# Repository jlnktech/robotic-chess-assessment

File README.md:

# robotic-chess-assessment
low cost chess robot

kicad folder contains schematic layout of hall effect detection using DRV5053. Idea is to scan 8 squares (1 row) at once, then repeat for other 7 rows to cut down on time. Each piece must have magnet attached.

pcb123 folder contains schematic layout of IR sensors using QRE1113. Once again, scan 1 row (8 squares) then repeat. Each piece must have reflect material on the bottom and be able to cover the slot on each of the squares.

CAD folder contains the mechanical layout of the xyz table

firmware folder contains arduino test for the z-axis portion

yet to be done is to add the raspberry pi actual chess code

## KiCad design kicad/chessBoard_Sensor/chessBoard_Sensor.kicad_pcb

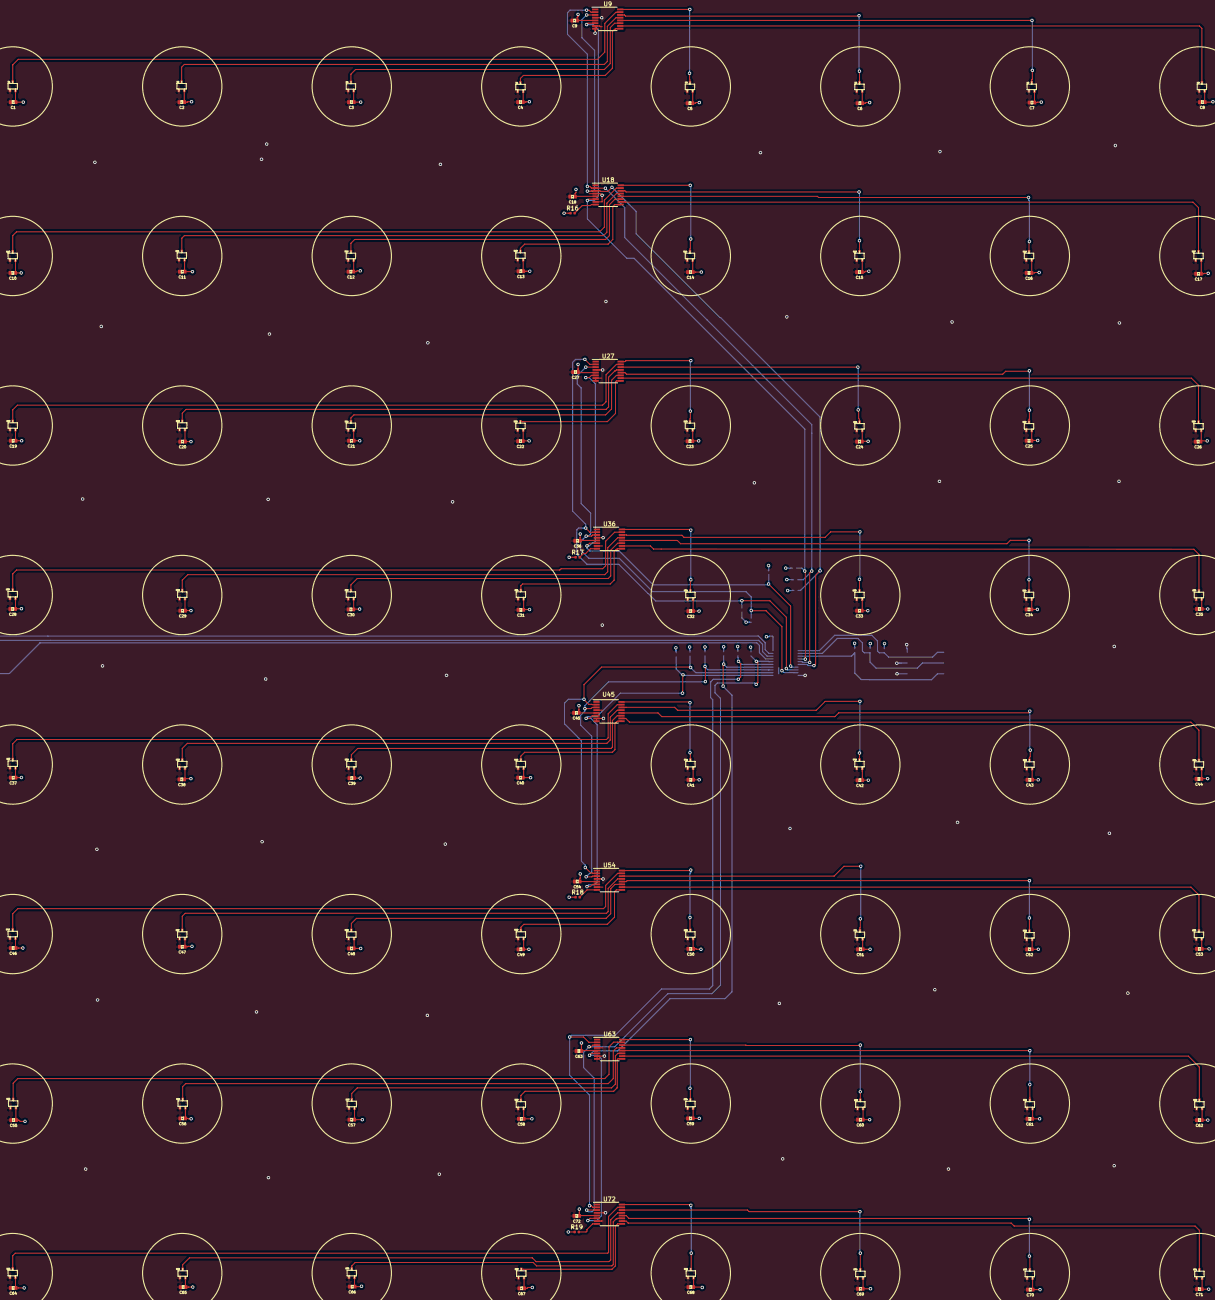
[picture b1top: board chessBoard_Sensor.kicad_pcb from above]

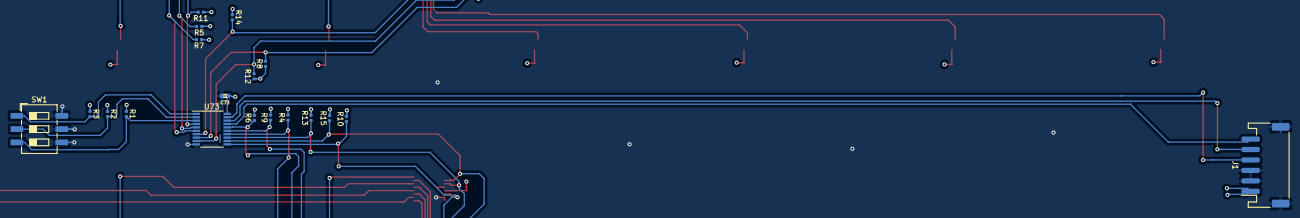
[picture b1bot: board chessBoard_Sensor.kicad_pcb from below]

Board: 4 copper layers, 167 parts (19 on the bottom side), 88 nets.

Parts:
C1, C2, C3, C4, C5, C6, C7, C8, C9, C10, C11, C12, C13, C14, C15, C16, C17, C18, C19, C20, C21, C22, C23, C24, C25, C26, C27, C28, C29, C30, C31, C32, C33, C34, C35, C36, C37, C38, C39, C40, C41, C42, C43, C44, C45, C46, C47, C48, C49, C50, C51, C52, C53, C54, C55, C56, C57, C58, C59, C60, C61, C62, C63, C64, C65, C66, C67, C68, C69, C70, C71, C72, C73: 0.1UF-0402-16V-10%; 0402
J1: HEADER_6; JST_PH_S6B-PH-SM4-TB_1x06-1MP_P2.00mm_Horizontal
R1, R2, R3, R4, R5, R6, R7, R8, R9, R10, R11, R12, R13, R14, R15, R16, R17, R18, R19: 10K, 5%, 402; R_0402_1005Metric
SW1: SW_DIP_x03; SW_DIP_SPSTx03_Slide_6.7x9.18mm_W8.61mm_P2.54mm_LowProfile
U1, U2, U3, U4, U5, U6, U7, U8, U10, U11, U12, U13, U14, U15, U16, U17, U19, U20, U21, U22, U23, U24, U25, U26, U28, U29, U30, U31, U32, U33, U34, U35, U37, U38, U39, U40, U41, U42, U43, U44, U46, U47, U48, U49, U50, U51, U52, U53, U55, U56, U57, U58, U59, U60, U61, U62, U64, U65, U66, U67, U68, U69, U70, U71: DRV5053VAQDBZR; sot323
U9, U18, U27, U36, U45, U54, U63, U72: ADC128D818; TSSOP-16_4.4x5mm_P0.65mm
U73: PCA9544APW; TSSOP-20_4.4x6.5mm_P0.65mm

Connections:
+3V3: C1.1, C2.1, C3.1, C4.1, C5.1, C6.1, C7.1, C8.1, C9.1, C10.1, C11.1, C12.1, C13.1, C14.1, C15.1, C16.1, C17.1, C18.1, C19.1, C20.1, C21.1, C22.1, C23.1, C24.1, C25.1, C26.1, C27.1, C28.1, C29.1, C30.1, C31.1, C32.1, C33.1, C34.1, C35.1, C36.1, C37.1, C38.1, C39.1, C40.1, C41.1, C42.1, C43.1, C44.1, C45.1, C46.1, C47.1, C48.1, C49.1, C50.1, C51.1, C52.1, C53.1, C54.1, C55.1, C56.1, C57.1, C58.1, C59.1, C60.1, C61.1, C62.1, C63.1, C64.1, C65.1, C66.1, C67.1, C68.1, C69.1, C70.1, C71.1, C72.1, C73.1, J1.1, R1.1, R2.1, R3.1, R4.2, R5.1, R6.2, R7.1, R8.1, R9.2, R10.2, R11.1, R12.1, R13.2, R14.1, R15.2, R16.1, R17.1, R18.1, R19.1, U1.3, U2.3, U3.3, U4.3, U5.3, U6.3, U7.3, U8.3, U9.5, U10.3, U11.3, U12.3, U13.3, U14.3, U15.3, U16.3, U17.3, U18.5, U19.3, U20.3, U21.3, U22.3, U23.3, U24.3, U25.3, U26.3, U27.5, U28.3, U29.3, U30.3, U31.3, U32.3, U33.3, U34.3, U35.3, U36.5, U37.3, U38.3, U39.3, U40.3, U41.3, U42.3, U43.3, U44.3, U45.5, U46.3, U47.3, U48.3, U49.3, U50.3, U51.3, U52.3, U53.3, U54.5, U55.3, U56.3, U57.3, U58.3, U59.3, U60.3, U61.3, U62.3, U63.5, U64.3, U65.3, U66.3, U67.3, U68.3, U69.3, U70.3, U71.3, U72.5, U73.20
/Sheet1/INT1: R11.2, U9.6, U18.6, U73.4
/Sheet1/SCL1: R7.2, U9.3, U18.3, U73.6
/Sheet1/SDA1: R5.2, U9.2, U18.2, U73.5
/sheet5C2B8B4A/INT4: R4.1, U63.6, U72.6, U73.14
/sheet5C2B8B4A/SCL4: R6.1, U63.3, U72.3, U73.16
/sheet5C2B8B4A/SDA4: R9.1, U63.2, U72.2, U73.15
/sheet5C2B89C0/INT3: R10.1, U45.6, U54.6, U73.11
/sheet5C2B89C0/SCL3: R13.1, U45.3, U54.3, U73.13
/sheet5C2B89C0/SDA3: R15.1, U45.2, U54.2, U73.12
/sheet5C2B878C/INT2: R14.2, U27.6, U36.6, U73.7
/sheet5C2B878C/SCL2: R12.2, U27.3, U36.3, U73.9
/sheet5C2B878C/SDA2: R8.2, U27.2, U36.2, U73.8
GND: C1.2, C2.2, C3.2, C4.2, C5.2, C6.2, C7.2, C8.2, C9.2, C10.2, C11.2, C12.2, C13.2, C14.2, C15.2, C16.2, C17.2, C18.2, C19.2, C20.2, C21.2, C22.2, C23.2, C24.2, C25.2, C26.2, C27.2, C28.2, C29.2, C30.2, C31.2, C32.2, C33.2, C34.2, C35.2, C36.2, C37.2, C38.2, C39.2, C40.2, C41.2, C42.2, C43.2, C44.2, C45.2, C46.2, C47.2, C48.2, C49.2, C50.2, C51.2, C52.2, C53.2, C54.2, C55.2, C56.2, C57.2, C58.2, C59.2, C60.2, C61.2, C62.2, C63.2, C64.2, C65.2, C66.2, C67.2, C68.2, C69.2, C70.2, C71.2, C72.2, C73.2, J1.2, J1.3, J1.MP, SW1.4, SW1.5, SW1.6, U1.1, U2.1, U3.1, U4.1, U5.1, U6.1, U7.1, U8.1, U9.4, U9.7, U9.8, U10.1, U11.1, U12.1, U13.1, U14.1, U15.1, U16.1, U17.1, U18.4, U18.7, U19.1, U20.1, U21.1, U22.1, U23.1, U24.1, U25.1, U26.1, U27.4, U27.7, U27.8, U28.1, U29.1, U30.1, U31.1, U32.1, U33.1, U34.1, U35.1, U36.4, U36.7, U37.1, U38.1, U39.1, U40.1, U41.1, U42.1, U43.1, U44.1, U45.4, U45.7, U45.8, U46.1, U47.1, U48.1, U49.1, U50.1, U51.1, U52.1, U53.1, U54.4, U54.7, U55.1, U56.1, U57.1, U58.1, U59.1, U60.1, U61.1, U62.1, U63.4, U63.7, U63.8, U64.1, U65.1, U66.1, U67.1, U68.1, U69.1, U70.1, U71.1, U72.4, U72.7, U73.10
unnamed: J1.4, U73.19
unnamed: J1.5, U73.18
unnamed: J1.6, U73.17
unnamed: R1.2, SW1.3, U73.3
unnamed: R2.2, SW1.2, U73.2
unnamed: R3.2, SW1.1, U73.1
unnamed: R16.2, U18.8
unnamed: R17.2, U36.8
unnamed: R18.2, U54.8
unnamed: R19.2, U72.8
unnamed: U1.2, U9.15
unnamed: U2.2, U9.13
unnamed: U3.2, U9.11
unnamed: U4.2, U9.9
unnamed: U5.2, U9.16
unnamed: U6.2, U9.14
unnamed: U7.2, U9.12
unnamed: U8.2, U9.10
unnamed: U10.2, U18.15
unnamed: U11.2, U18.13
unnamed: U12.2, U18.11
unnamed: U13.2, U18.9
unnamed: U14.2, U18.16
unnamed: U15.2, U18.14
unnamed: U16.2, U18.12
unnamed: U17.2, U18.10
unnamed: U19.2, U27.15
unnamed: U20.2, U27.13
unnamed: U21.2, U27.11
unnamed: U22.2, U27.9
unnamed: U23.2, U27.16
unnamed: U24.2, U27.14
unnamed: U25.2, U27.12
unnamed: U26.2, U27.10
unnamed: U28.2, U36.15
unnamed: U29.2, U36.13
unnamed: U30.2, U36.11
unnamed: U31.2, U36.9
unnamed: U32.2, U36.16
unnamed: U33.2, U36.14
unnamed: U34.2, U36.12
unnamed: U35.2, U36.10
unnamed: U37.2, U45.15
unnamed: U38.2, U45.13
unnamed: U39.2, U45.11
unnamed: U40.2, U45.9
unnamed: U41.2, U45.16
unnamed: U42.2, U45.14
unnamed: U43.2, U45.12
unnamed: U44.2, U45.10
unnamed: U46.2, U54.15
unnamed: U47.2, U54.13
unnamed: U48.2, U54.11
unnamed: U49.2, U54.9
unnamed: U50.2, U54.16
unnamed: U51.2, U54.14
unnamed: U52.2, U54.12
unnamed: U53.2, U54.10
unnamed: U55.2, U63.15
unnamed: U56.2, U63.13
unnamed: U57.2, U63.11
unnamed: U58.2, U63.9
unnamed: U59.2, U63.16
unnamed: U60.2, U63.14
unnamed: U61.2, U63.12
unnamed: U62.2, U63.10
unnamed: U64.2, U72.15
unnamed: U65.2, U72.13
unnamed: U66.2, U72.11
unnamed: U67.2, U72.9
unnamed: U68.2, U72.16
unnamed: U69.2, U72.14
unnamed: U70.2, U72.12
unnamed: U71.2, U72.10

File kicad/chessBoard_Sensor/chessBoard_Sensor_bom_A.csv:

Component,Description,Part,References,Value,Footprint,Quantity Per PCB,Datasheet,Field4,Category,Status,Family,MPN,Digi-Key_PN,DK_Datasheet_Link,DK_Detail_Page,Manufacturer
1,0.1uF ceramic capacitors A capacitor is a passive two-terminal electrical component used to store electrical energy temporarily in an electric field.,0.1UF-0402-16V-10%,C1 C2 C3 C4 C5 C6 C7 C8 C9 C10 C11 C12 C13 C14 C15 C16 C17 C18 C19 C20 C21 C22 C23 C24 C25 C26 C27 C28 C29 C30 C31 C32 C33 C34 C35 C36 C37 C38 C39 C40 C41 C42 C43 C44 C45 C46 C47 C48 C49 C50 C51 C52 C53 C54 C55 C56 C57 C58 C59 C60 C61 C62 C63 C64 C65 C66 C67 C68 C69 C70 C71 C72 C73,0.1UF-0402-16V-10%,0402,73,,CAP-12416,,,,,,,,
2,,HEADER_6,J1,HEADER_6,JST_PH_S6B-PH-SM4-TB_1x06-1MP_P2.00mm_Horizontal,1,,,,,,,,,,
3,Resistor,R,R1 R2 R3 R4 R5 R6 R7 R8 R9 R10 R11 R12 R13 R14 R15 R16 R17 R18 R19,"10K, 5%, 402",R_0402_1005Metric,19,~,,,,,,,,,
4,"3x DIP Switch, Single Pole Single Throw (SPST) switch, small symbol",SW_DIP_x03,SW1,SW_DIP_x03,SW_DIP_SPSTx03_Slide_6.7x9.18mm_W8.61mm_P2.54mm_LowProfile,1,,,,,,,,,,
5,"12-Bit, 8-Channel, ADC System Monitor With Temperature Sensor, I2C Interface, TSSOP-16",ADC128D818,U9 U18 U27 U36 U45 U54 U63 U72,ADC128D818,TSSOP-16_4.4x5mm_P0.65mm,8,http://www.ti.com/lit/ds/symlink/adc128d818.pdf,,,,,,,,,
6,SENSOR LINEAR ANALOG SOT23-3,DRV5053VAQDBZR,U1 U2 U3 U4 U5 U6 U7 U8 U10 U11 U12 U13 U14 U15 U16 U17 U19 U20 U21 U22 U23 U24 U25 U26 U28 U29 U30 U31 U32 U33 U34 U35 U37 U38 U39 U40 U41 U42 U43 U44 U46 U47 U48 U49 U50 U51 U52 U53 U55 U56 U57 U58 U59 U60 U61 U62 U64 U65 U66 U67 U68 U69 U70 U71,DRV5053VAQDBZR,sot323,64,http://www.ti.com/lit/ds/symlink/drv5053.pdf,,"Sensors, Transducers",Active,"Magnetic Sensors - Linear, Compass (ICs)",DRV5053VAQDBZR,296-38460-1-ND,http://www.ti.com/lit/ds/symlink/drv5053.pdf,/product-detail/en/texas-instruments/DRV5053VAQDBZR/296-38460-1-ND/5022225,Texas Instruments
7,"4-channel I2C-bus multiplexer with interrupt logic, TSSOP20 package",PCA9544APW,U73,PCA9544APW,TSSOP-20_4.4x6.5mm_P0.65mm,1,http://www.nxp.com/documents/data_sheet/PCA9544A.pdf,,,,,,,,,





Component Groups:,7
Component Count:,167
Fitted Components:,167
Number of PCBs:,1
Total components:,167
Schematic Version:,A
Schematic Date:,2019-01-01
BoM Date:,Fri 04 Jan 2019 08:12:23 PM PST
Schematic Source:,/home/jlnktech/workspace/kicad_projects/chessBoard_Sensor/chessBoard_Sensor.sch
KiCad Version:,Eeschema 6.0.0-rc1-unknown-62e2fe8~66~ubuntu18.04.1
